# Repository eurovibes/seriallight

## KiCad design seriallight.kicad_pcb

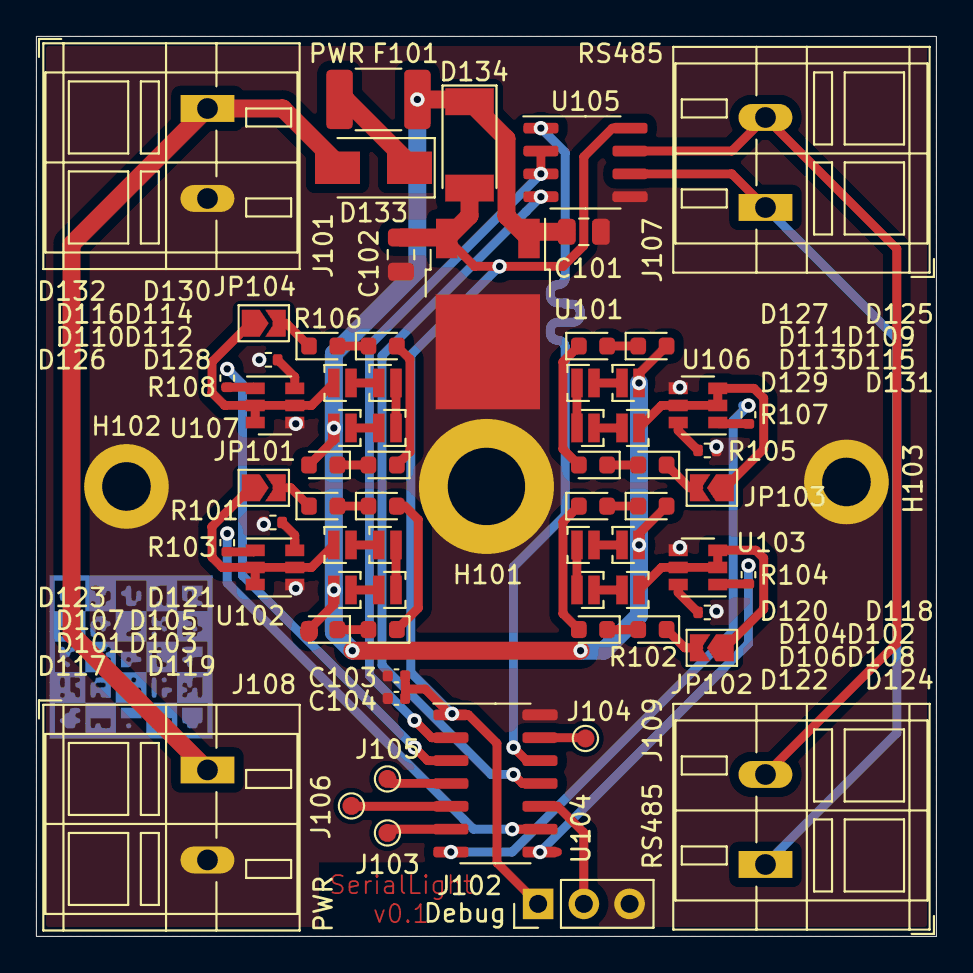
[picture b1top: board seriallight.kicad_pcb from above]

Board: 2 copper layers, 50.0 x 50.0 mm, 70 parts (0 on the bottom side), 59 nets.

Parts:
C101: 10µ; C_0805_2012Metric
C102: 22µ; C_0805_2012Metric
C103: 1µ; C_0402_1005Metric
C104: 100n; C_0402_1005Metric
D101, D102, D103, D104, D105, D106, D107, D108, D109, D110, D111, D112, D113, D114, D115, D116: LED; LED_Cree-XQ
D117, D119, D121, D123: red; LED_0603_1608Metric
D118, D120, D122, D124: green; LED_0603_1608Metric
D125, D127, D129, D131: blue; LED_0603_1608Metric
D126, D128, D130, D132: white; LED_0603_1608Metric
D133: SS14; D_SMA
D134: SM4007; D_MELF
F101: 750mA; Fuse_1812_4532Metric_Castellated
H101: MountingHole_4.3mm_M4_DIN965_Pad
H102, H103: MountingHole_2.7mm_M2.5_DIN965_Pad
J101, J108: PWR; TerminalBlock_WAGO_236-102_1x02_P5.00mm_45Degree
J102: Debug; PinHeader_1x03_P2.54mm_Vertical
J103: IO3; TestPoint_Pad_D1.0mm
J104: IO0; TestPoint_Pad_D1.0mm
J105: IO1; TestPoint_Pad_D1.0mm
J106: IO2; TestPoint_Pad_D1.0mm
J107, J109: RS485; TerminalBlock_WAGO_236-102_1x02_P5.00mm_45Degree
JP101: R; SolderJumper-2_P1.3mm_Open_TrianglePad1.0x1.5mm
JP102: G; SolderJumper-2_P1.3mm_Open_TrianglePad1.0x1.5mm
JP103: B; SolderJumper-2_P1.3mm_Open_TrianglePad1.0x1.5mm
JP104: W; SolderJumper-2_P1.3mm_Open_TrianglePad1.0x1.5mm
R101, R102, R105, R106: 82; R_0402_1005Metric
R103, R104, R107, R108: 1k; R_0402_1005Metric
U101: L78M05; TO-252-2
U102, U103, U106, U107: BCR421UW6; SOT-23-6
U104: ATtiny404-SS; SOIC-14_3.9x8.7mm_P1.27mm
U105: SP3485CN; SOIC-8_3.9x4.9mm_P1.27mm

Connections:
+5V: C102.1, C103.1, C104.1, D134.2, J102.1, U101.3, U104.1, U105.8
+12V: C101.1, D101.2, D102.2, D109.2, D110.2, D117.2, D118.2, D125.2, D126.2, D134.1, F101.1, U101.1
+VDC: D133.2, J101.1, J108.1
/B: R107.2, U104.7
/G: R104.2, U104.8
/R: R103.2, U104.9
/W: R108.2, U104.3
GND: C101.2, C102.2, C103.2, C104.2, H101.1, H102.1, H103.1, J101.2, J102.3, J108.2, R101.1, R102.1, R105.1, R106.1, U101.2, U102.4, U103.4, U104.14, U105.5, U106.4, U107.4
unnamed: D101.1, D103.2
unnamed: D102.1, D104.2
unnamed: D103.1, D105.2
unnamed: D104.1, D106.2
unnamed: D105.1, D107.2
unnamed: D106.1, D108.2
unnamed: D107.1, JP101.1, U102.2, U102.3, U102.5
unnamed: D108.1, JP102.1, U103.2, U103.3, U103.5
unnamed: D109.1, D111.2
unnamed: D110.1, D112.2
unnamed: D111.1, D113.2
unnamed: D112.1, D114.2
unnamed: D113.1, D115.2
unnamed: D114.1, D116.2
unnamed: D115.1, JP103.1, U106.2, U106.3, U106.5
unnamed: D116.1, JP104.1, U107.2, U107.3, U107.5
unnamed: D117.1, D119.2
unnamed: D118.1, D120.2
unnamed: D119.1, D121.2
unnamed: D120.1, D122.2
unnamed: D121.1, D123.2
unnamed: D122.1, D124.2
unnamed: D123.1, JP101.2
unnamed: D124.1, JP102.2
unnamed: D125.1, D127.2
unnamed: D126.1, D128.2
unnamed: D127.1, D129.2
unnamed: D128.1, D130.2
unnamed: D129.1, D131.2
unnamed: D130.1, D132.2
unnamed: D131.1, JP103.2
unnamed: D132.1, JP104.2
unnamed: D133.1, F101.2
unnamed: J102.2, U104.10
unnamed: J103.1, U104.6
unnamed: J104.1, U104.13
unnamed: J105.1, U104.4
unnamed: J106.1, U104.5
unnamed: J107.1, J109.1, U105.6
unnamed: J107.2, J109.2, U105.7
unnamed: R101.2, U102.6
unnamed: R102.2, U103.6
unnamed: R103.1, U102.1
unnamed: R104.1, U103.1
unnamed: R105.2, U106.6
unnamed: R106.2, U107.6
unnamed: R107.1, U106.1
unnamed: R108.1, U107.1
unnamed: U104.2, U105.2, U105.3
unnamed: U104.11, U105.4
unnamed: U104.12, U105.1

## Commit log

2021-06-03 Initial
2021-06-03 Order v0.1
